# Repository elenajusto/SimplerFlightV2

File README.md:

# SimplerFlightV2

## Architecture

## Simulations
Simulations done using Falstad. Available at: https://www.falstad.com/circuit/

### Buzzer

hFE value of 250 

As per characteristics of FSB560A NPN BJT at https://www.digikey.com/en/products/detail/onsemi/FSB560A/1049460

### Camera Power

Beta value of 7.8

Assuming:
- RDS(on) (Ω) (use typical value): 0.16
- VGS where measured (V): 2.5
- Threshold (V) (use typical value): 3.3

As per characteristics of BSS816NWH6327XTSA1 N-MOSFET at https://www.digikey.com.au/en/products/detail/infineon-technologies/BSS816NWH6327XTSA1/5959970

## Microcontroller Pinout

## Schematic

### Root

### Microcontroller

### Power

### Sensors

### Storage

### Peripherals

### Headers

## Routing

## PCB

## Dimensions
94mm x 74mm

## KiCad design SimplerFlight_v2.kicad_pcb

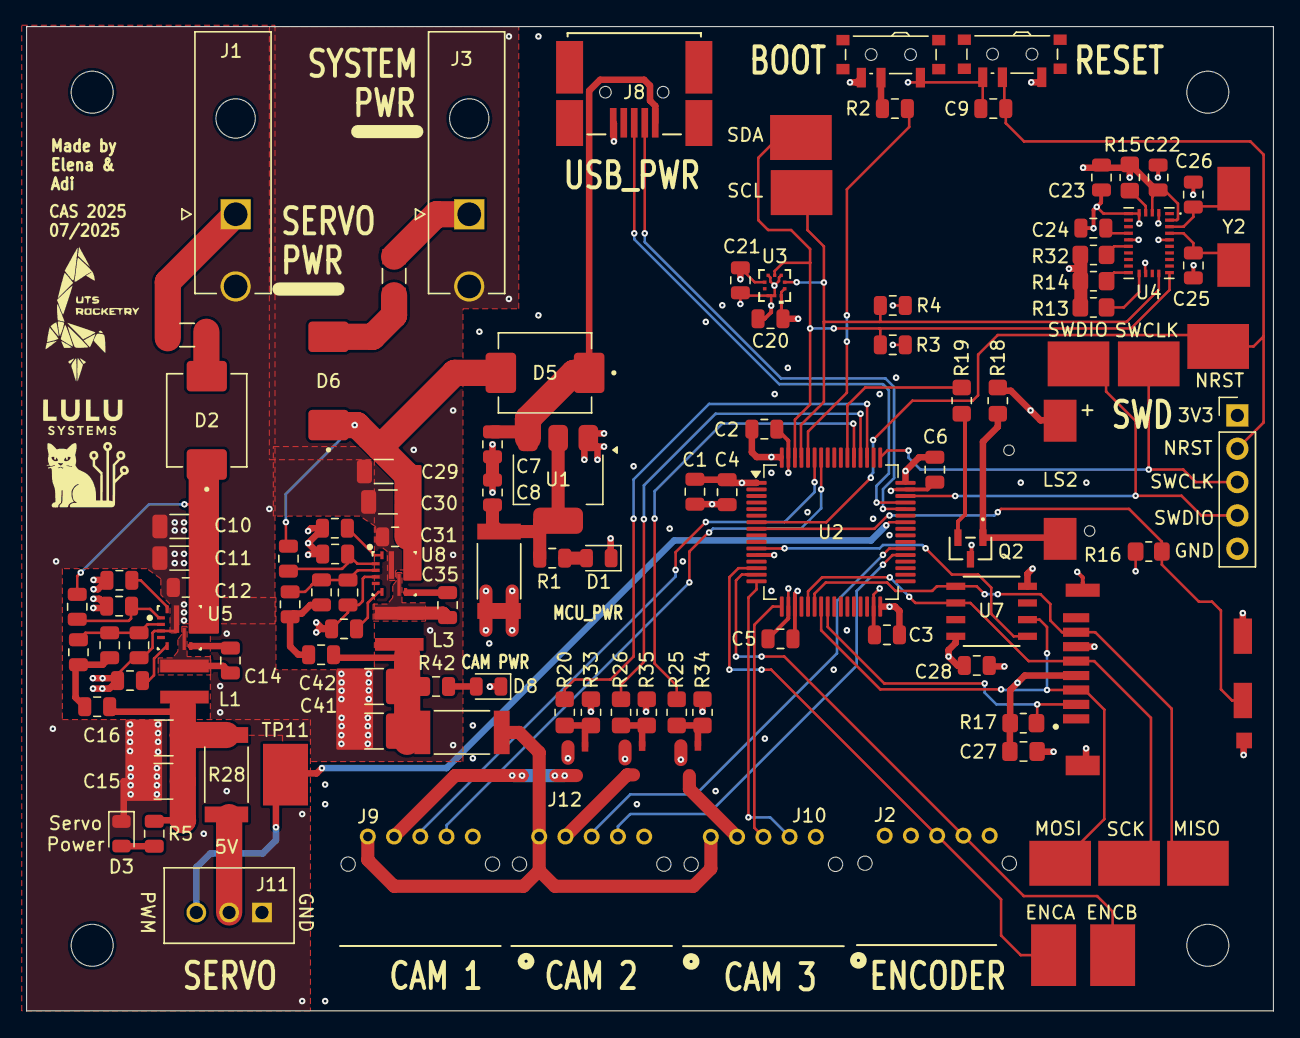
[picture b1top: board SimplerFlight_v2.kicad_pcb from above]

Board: 4 copper layers, 95.0 x 75.0 mm, 119 parts (0 on the bottom side), 74 nets.

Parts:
C1, C7: 10uF; C_0805_2012Metric
C2, C3, C4, C5, C6, C9, C20, C21, C22, C23, C24, C28: 100nF; C_0805_2012Metric
C8: 22uF; C_0805_2012Metric
C10, C11, C29, C30: 10uF; C_1206_3216Metric
C12, C14, C31, C35: 0.1uF; C_0805_2012Metric
C13, C34: 47nF; C_0805_2012Metric
C15, C16, C41, C42: 10uF; C_1210_3225Metric
C17, C40: 150pF; C_0805_2012Metric
C25, C26: 15pF; C_0805_2012Metric
C27: 100nF; C_0805_2012Metric_Pad1.18x1.45mm_HandSolder
D1: BLUE; LED_0805_2012Metric
D2, D5, D6: B540C-13-F; DIOM6959X245N
D3, D8: RED; LED_0805_2012Metric
ENCA: 5016; KEYSTONE_5016
ENCB: 5016; KEYSTONE_5016
F1, F3: C1F-5; FUSC3215X83N
H1, H2, H3, H4: MountingHole; MountingHole_3.2mm_M3
J1, J3: Battery 1; MOLEX_1724480002
J2: Encoder; CONN_S05B-PASK-2_JST
J8: USB; CON00317_5_MOL
J9, J10, J12: Cam 1; CONN_S05B-PASK-2_JST
J11: Servo; JST_B3B-XH-A
J13: SWD Header; PinHeader_1x05_P2.54mm_Vertical
J14: DM3CS-SF; HRS_DM3CS-SF
L1, L3: 3.3uH; WE-MAPI_4030
LS2: CBT-09427-SMT; CUI_CBT-09427-SMT
MISO: 5016; KEYSTONE_5016
MOSI: 5016; KEYSTONE_5016
NRST: 5016; KEYSTONE_5016
Q2: NPN; SSOT3_3X1P5_ONS
Q5, Q6, Q7: BSS816NWH6327XTSA1; SOT65P210X100-3N
R1, R3, R4, R5, R42: 1k5; C_0805_2012Metric
R2: 10k; C_0805_2012Metric
R6, R36: 169kR; C_0805_2012Metric
R7, R37: 36.1kR; C_0805_2012Metric
R8, R38: 52.3kR; C_0805_2012Metric
R9, R40: 49.9R; C_0805_2012Metric
R10, R41: 73.2kR; C_0805_2012Metric
R11, R39: 10kR; C_0805_2012Metric
R13, R14: 2.2kR; R_0805_2012Metric_Pad1.20x1.40mm_HandSolder
R15, R33, R34, R35: 10kR; R_0805_2012Metric_Pad1.20x1.40mm_HandSolder
R16, R17, R32: 10k; R_0805_2012Metric_Pad1.20x1.40mm_HandSolder
R18: 1kR; R_0805_2012Metric_Pad1.20x1.40mm_HandSolder
R19: 470; R_0805_2012Metric_Pad1.20x1.40mm_HandSolder
R20, R25, R26: 100R; R_0805_2012Metric_Pad1.20x1.40mm_HandSolder
R27, R28, R29: CSRN2512FKR500; RESC6331X70N
SCK: 5016; KEYSTONE_5016
SCL: 5016; KEYSTONE_5016
SDA: 5016; KEYSTONE_5016
SW1: Boot Switch; SW_SPDT_PCM12
SW2: System Reset; SW_SPDT_PCM12
SWCLK: 5016; KEYSTONE_5016
SWDIO: 5016; KEYSTONE_5016
TP11: 5016; KEYSTONE_5016
U1: AMS1117-3.3; SOT-223-3_TabPin2
U2: STM32F401RETx; LQFP-64_10x10mm_P0.5mm
U3: BMP581; QFN10_BMP581_BOS
U4: BNO085; IC_BNO085
U5, U8: TPS56A37RPAR; RPA0010A-MFG
U7: MX25V4006EM1I-13G; SOP8_150_MAC
Y2: Crystal; Crystal_SMD_0603-2Pin_6.0x3.5mm_HandSoldering

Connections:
/BOARD_3V3: C1.1, C2.1, C3.1, C4.1, C5.1, C6.1, C20.1, C21.1, C22.1, C23.1, C27.1, C28.1, J2.1, J13.1, J14.4 (VDD), LS2.P, R3.2, R4.2, R13.1, R14.1, R15.2, R16.1, R17.1, R18.2, R29.2, R32.1, R33.2, R34.2, R35.2, SW1.3 (C), SW2.1 (A), U2.1 (VBAT), U2.19 (VDD), U2.32 (VDD), U2.48 (VDD), U2.64 (VDD), U3.1 (VDDIO), U3.6 (CSB), U3.10 (VDD), U4.3 (VDD), U4.28 (VDDIO), U7.8 (VCC)
/Headers/SYS_JTCK-SWCLK: J13.3, SWCLK.TP, U2.49 (PA14)
/Headers/SYS_JTMS-SWDIO: J13.4, SWDIO.TP, U2.46 (PA13)
/Microcontroller/BOOT0: R2.2, U2.60 (BOOT0)
/Microcontroller/BUZZ: R19.1, U2.54 (PD2)
/Microcontroller/CAM_1_EN: R20.1, U2.51 (PC10)
/Microcontroller/CAM_2_EN: R25.1, U2.53 (PC12)
/Microcontroller/CAM_3_EN: R26.1, U2.52 (PC11)
/Microcontroller/ENC_A: ENCA.TP, J2.3, U2.14 (PA0)
/Microcontroller/ENC_B: ENCB.TP, J2.4, U2.15 (PA1)
/Microcontroller/FLASH_MEM_CS: U2.11 (PC3), U7.1 (CS#)
/Microcontroller/I2C1_SCL: R4.1, SCL.TP, U2.61 (PB8), U3.2 (SCK), U4.19 (H_SCL/SCK/RX)
/Microcontroller/I2C1_SDA: R3.1, SDA.TP, U2.62 (PB9), U3.4 (SDI), U4.20 (H_SDA/H_MISO/TX)
/Microcontroller/SD_DET: J14.9 (CD_SW), R16.2, U2.8 (PC0)
/Microcontroller/SD_MEM_CS: J14.2 (CD/DAT3), R17.2, U2.24 (PC4)
/Microcontroller/SERVO_PWM: J11.3, TP11.TP, U2.42 (PA9)
/Microcontroller/SP1_MISO: J14.7 (DAT0), MISO.TP, U2.22 (PA6), U7.5 (SI/SIO0)
/Microcontroller/SP1_MOSI: J14.3 (CMD), MOSI.TP, U2.23 (PA7), U7.2 (SO/SIO1)
/Microcontroller/SP1_SCK: J14.5 (CLK), SCK.TP, U2.21 (PA5), U7.6 (SCLK)
/Microcontroller/SW_BOOT0: R2.1, SW1.2 (B)
/Microcontroller/USART1_RX: J9.3, U2.59 (PB7)
/Microcontroller/USART1_TX: J9.4, U2.58 (PB6)
/Microcontroller/USART2_RX: J10.3, U2.17 (PA3)
/Microcontroller/USART2_TX: J10.4, U2.16 (PA2)
/Microcontroller/USART6_RX: J12.3, U2.38 (PC7)
/Microcontroller/USART6_TX: J12.4, U2.37 (PC6)
/Microcontroller/USB_DN: J8.2, U2.44 (PA11)
/Microcontroller/USB_DP: J8.3, U2.45 (PA12)
/Peripherals/5V_CAM: J9.1, J10.1, J12.1, R27.2
/Peripherals/5V_SERVO: J11.2, R28.2
/Power/5V_CAM: C41.1, C42.1, L3.2, R27.1, R40.1, R42.1
/Power/5V_SERVO: C15.1, C16.1, L1.2, R5.1, R9.1, R28.1
/Power/+3V3: C8.1, R1.1, R29.1, U1.2 (VO)
/Power/BAT_1: D2.A, F1.2
/Power/BAT_2: D6.A, F3.2
/Power/BT_CAM: C35.1, U8.7 (BOOT)
/Power/BT_SERVO: C14.1, U5.7 (BOOT)
/Power/EN_CAM_PWR: R36.2, R37.1, U8.1 (EN)
/Power/EN_SERVO_PWR: R6.2, R7.1, U5.1 (EN)
/Power/FB_CAM_PWR: C40.2, R39.1, R41.2, U8.2 (FB)
/Power/FB_SERVO: C17.2, R10.2, R11.1, U5.2 (FB)
/Power/MODE_CAM: R38.2, U8.10 (MODE)
/Power/MODE_SRVO: R8.2, U5.10 (MODE)
/Power/SS_CAM: C34.1, U8.5 (SS)
/Power/SS_SERVO: C13.1, U5.5 (SS)
/Power/SW_CAM_PWR: C35.2, L3.1, U8.6 (SW)
/Power/SW_SERVO: C14.2, L1.1, U5.6 (SW)
/Power/VBUS_MCU: C7.1, D5.C, J8.1, U1.3 (VI)
/Power/VIN_CAM: C29.1, C30.1, C31.1, D5.A, D6.C, R36.1, U8.8 (VIN)
/Power/VIN_SERVO: C10.1, C11.1, C12.1, D2.C, R6.1, U5.8 (VIN)
GND: C1.2, C2.2, C3.2, C4.2, C5.2, C6.2, C7.2, C8.2, C9.2, C10.2, C11.2, C12.2, C13.2, C15.2, C16.2, C20.2, C21.2, C22.2, C23.2, C24.1, C25.2, C26.2, C27.2, C28.2, C29.2, C30.2, C31.2, C34.2, C41.2, C42.2, D1.1 (K), D3.1 (K), D8.1 (K), J1.2, J2.2, J3.2, J8.5, J11.1, J13.5, J14.6 (VSS), J14.S1 (GND), J14.S2 (GND__1), J14.S3 (GND__2), J14.S5 (GND__3), Q2.3 (E), Q5.2 (S), Q6.2 (S), Q7.2 (S), R7.2, R8.1, R11.2, R37.2, R38.1, R39.2, SW1.1 (A), SW2.3 (C), U1.1 (GND), U2.12 (VSSA), U2.18 (VSS), U2.31 (VSS), U2.47 (VSS), U2.63 (VSS), U3.3 (VSS), U3.5 (SDO), U3.8 (VSS), U3.9 (VSS), U4.2 (GND), U4.5 (PS1), U4.6 (PS0/WAKE), U4.10 (CLKSEL0), U4.17 (SA0/H_MOSI), U4.25 (GNDIO), U5.3 (AGND), U5.9 (PGND), U7.4 (GND), U8.3 (AGND), U8.9 (PGND)
NRST: C9.1, J13.2, NRST.TP, SW2.2 (B), U2.7 (NRST)
unnamed: C17.1, R9.2, R10.1
unnamed: C40.1, R40.2, R41.1
unnamed: D1.2 (A), R1.2
unnamed: D3.2 (A), R5.2
unnamed: D8.2 (A), R42.2
unnamed: F1.1, J1.1
unnamed: F3.1, J3.1
unnamed: Q2.2 (B), R19.2
unnamed: LS2.M, Q2.1 (C), R18.1
unnamed: J9.2, Q5.3 (D)
unnamed: Q5.1 (G), R20.2, R33.1
unnamed: J10.2, Q6.3 (D)
unnamed: Q6.1 (G), R25.2, R34.1
unnamed: J12.2, Q7.3 (D)
unnamed: Q7.1 (G), R26.2, R35.1
unnamed: C24.2, U4.9 (CAP)
unnamed: R14.2, U4.15 (ENV_SCL)
unnamed: R13.2, U4.16 (ENV_SDA)
unnamed: C26.1, U4.27 (XIN32), Y2.2
unnamed: C25.1, U4.26 (XOUT32/CLKSEL1), Y2.1
unnamed: R15.1, U4.4 (~BOOT)
unnamed: R32.2, U4.11 (~RST)

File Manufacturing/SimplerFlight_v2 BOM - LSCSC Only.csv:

JLCPCB Part #,Comment,Footprint,Designator
C28233,100nF,Capacitor_SMD:C_0805_2012Metric,"C2,C3,C4,C5,C6,C9,C20,C21,C18,C19,C27,C28"
C45783,22uF,Capacitor_SMD:C_0805_2012Metric," ""C1"
C13585,10uF,Capacitor_SMD:C_1206_3216Metric,"C10,C11,C29,C30"
C28378,0.1uF,Capacitor_SMD:C_0805_2012Metric,"C12,C14,C31,C35"
C53134,47nF,Capacitor_SMD:C_0805_2012Metric,"C13,C34"
C138687,10uF,Capacitor_SMD:C_1210_3225Metric,"C15,C16,C41,C42"
C1716,150pF,Capacitor_SMD:C_0805_2012Metric,"C17,C40"
C107110,15pF,Capacitor_SMD:C_0805_2012Metric,"C25,C26"
C2297,BLUE,LED_SMD:LED_0805_2012Metric,D1
C72264,B540C-13-F,B540C_13_F:DIOM6959X245N,"D2,D5,D6"
C2286,RED,LED_SMD:LED_0805_2012Metric,"D3,D8"
" 	C57525",C1F-5,C1F_5:FUSC3215X83N,"F1,F3"
C5188718,Battery 1,1724480002:MOLEX_1724480002,"J1,J3"
C598519,USB,custom,J4
C2845127,Cam 1,S05B_PASK_2_LF__SN_:CONN_S05B-PASK-2_JST,"J2, J9,J10,J12"
C144394,Servo,B3B_XH_A:JST_B3B-XH-A,J11
C202111,DM3CS-SF,DM3CS_SF:HRS_DM3CS-SF,J14
C39676082,3.3uH,74438357033:WE-MAPI_4030,"L1,L3"
C95299,Huaneng MLT-7525,LS2,LS2
C236952,NPN,FSB560A:SSOT3_3X1P5_ONS,Q2
C22366684,BSS816NWH6327XTSA1,SOT65P210X100-3N,"Q5,Q6,Q7"
C4310,1k5,Capacitor_SMD:C_0805_2012Metric,"R1,R3,R4,R5,R42"
C2933337,169kR,Capacitor_SMD:C_0805_2012Metric,"R6,R36"
C2758300,52.3kR,Capacitor_SMD:C_0805_2012Metric,"R8,R38"
C269747,49.9R,Capacitor_SMD:C_0805_2012Metric,"R9,R40"
C865640,73.2kR,Capacitor_SMD:C_0805_2012Metric,"R10,R41"
C17414,10kR,Capacitor_SMD:C_0805_2012Metric,"R2, R11,R39, R15,R33,R34,R35, R16,R17,R32"
C17513,1kR,Resistor_SMD:R_0805_2012Metric_Pad1.20x1.40mm_HandSolder,R18
C17710,470,Resistor_SMD:R_0805_2012Metric_Pad1.20x1.40mm_HandSolder,R19
C17408,100R,Resistor_SMD:R_0805_2012Metric_Pad1.20x1.40mm_HandSolder,"R20,R25,R26"
C346810,CSRN2512FKR500,CSRN2512FKR500:RESC6331X70N,"R27,R28,R29"
 C221841,Boot Switch,Button_Switch_SMD:SW_SPDT_PCM12,"SW1, SW2"
C238129,5016,5016:KEYSTONE_5016,"TP1,TP2,TP3,TP4,TP5,TP6,TP7,TP8,TP11,TP12,TP13"
C6186,AMS1117-3.3,Package_TO_SOT_SMD:SOT-223-3_TabPin2,U1
C116978,STM32F401RETx,Package_QFP:LQFP-64_10x10mm_P0.5mm,U2
C5362283,BMP581,BMP581:QFN10_BMP581_BOS,U3
C2836813,BMI270," 	LGA-14(2.5x3)",U4
 C22392669,TPS56A37RPAR,RPA0010A-MFG,"U5,U8"
C152601,MX25V4006EM1I-13G,SOP8_150_MAC,U7
C130253,32 kHz,ABS07_32_768KHZ_T:XTAL_ABS07-32.768KHZ-T,Y2

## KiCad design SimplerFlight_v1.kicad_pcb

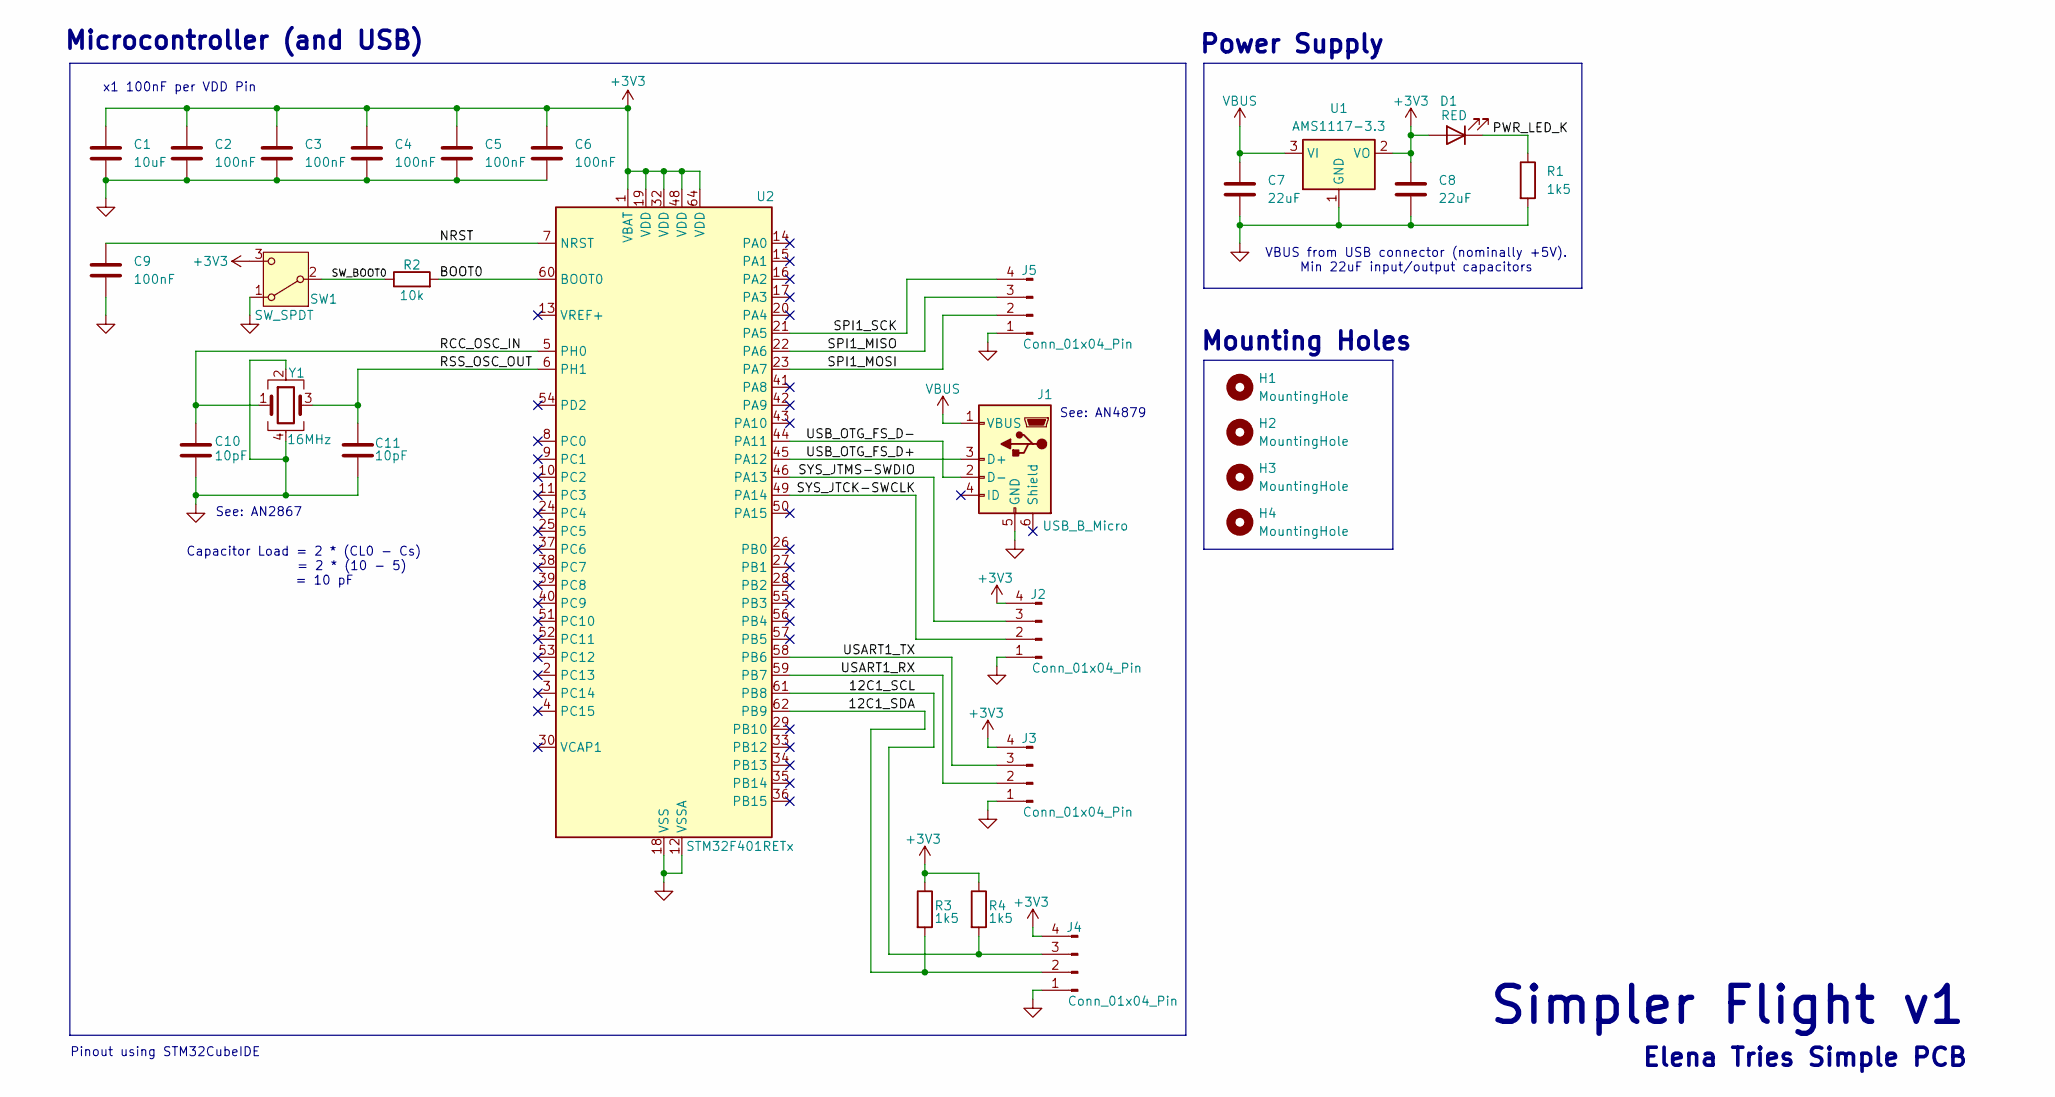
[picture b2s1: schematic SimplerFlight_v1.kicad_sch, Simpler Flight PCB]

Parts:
C1: 10uF; C_0805_2012Metric
C2, C3, C4, C5, C6, C9: 100nF; C_0805_2012Metric
C7, C8: 22uF; C_0805_2012Metric
C10, C11: 10pF; C_0805_2012Metric
D1: RED; LED_0805_2012Metric
H1, H2, H3, H4: MountingHole; MountingHole_2.2mm_M2
J1: USB_B_Micro; USB_Micro-B_Wuerth_629105150521
J2, J3, J4, J5: Conn_01x04_Pin; PinHeader_1x04_P2.54mm_Vertical
R1, R3, R4: 1k5; C_0805_2012Metric
R2: 10k; C_0805_2012Metric
SW1: SW_SPDT; SW_SPDT_PCM12
U1: AMS1117-3.3; SOT-223-3_TabPin2
U2: STM32F401RETx; LQFP-64_10x10mm_P0.5mm
Y1: 16MHz; Crystal_SMD_3225-4Pin_3.2x2.5mm

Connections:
+3V3: C1.1, C2.1, C3.1, C4.1, C5.1, C6.1, C8.1, D1.2 (A), J2.4, J3.4, J4.4, R3.1, R4.1, SW1.3 (C), U1.2 (VO), U2.1 (VBAT), U2.19 (VDD), U2.32 (VDD), U2.48 (VDD), U2.64 (VDD)
/12C1_SCL: J4.3, R4.2, U2.61 (PB8)
/12C1_SDA: J4.2, R3.2, U2.62 (PB9)
/BOOT0: R2.2, U2.60 (BOOT0)
/NRST: C9.1, U2.7 (NRST)
/PWR_LED_K: D1.1 (K), R1.1
/RCC_OSC_IN: C10.1, U2.5 (PH0), Y1.1
/RSS_OSC_OUT: C11.1, U2.6 (PH1), Y1.3
/SPI1_MISO: J5.3, U2.22 (PA6)
/SPI1_MOSI: J5.2, U2.23 (PA7)
/SPI1_SCK: J5.4, U2.21 (PA5)
/SW_BOOT0: R2.1, SW1.2 (B)
/SYS_JTCK-SWCLK: J2.2, U2.49 (PA14)
/SYS_JTMS-SWDIO: J2.3, U2.46 (PA13)
/USART1_RX: J3.2, U2.59 (PB7)
/USART1_TX: J3.3, U2.58 (PB6)
/USB_OTG_FS_D+: J1.3 (D+), U2.45 (PA12)
/USB_OTG_FS_D-: J1.2 (D-), U2.44 (PA11)
GND: C1.2, C2.2, C3.2, C4.2, C5.2, C6.2, C7.2, C8.2, C9.2, C10.2, C11.2, J1.5 (GND), J2.1, J3.1, J4.1, J5.1, R1.2, SW1.1 (A), U1.1 (GND), U2.12 (VSSA), U2.18 (VSS), U2.31 (VSS), U2.47 (VSS), U2.63 (VSS), Y1.2, Y1.4
VBUS: C7.1, J1.1 (VBUS), U1.3 (VI)

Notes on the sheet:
x1 100nF per VDD Pin
Pinout using STM32CubeIDE
VBUS from USB connector (nominally +5V). Min 22uF input/output capacitors
Capacitor Load = 2 * (CL0 - Cs) = 2 * (10 - 5) = 10 pF
Mounting Holes
See: AN4879
Elena Tries Simple PCB
See: AN2867
Power Supply
Simpler Flight v1
Microcontroller (and USB)

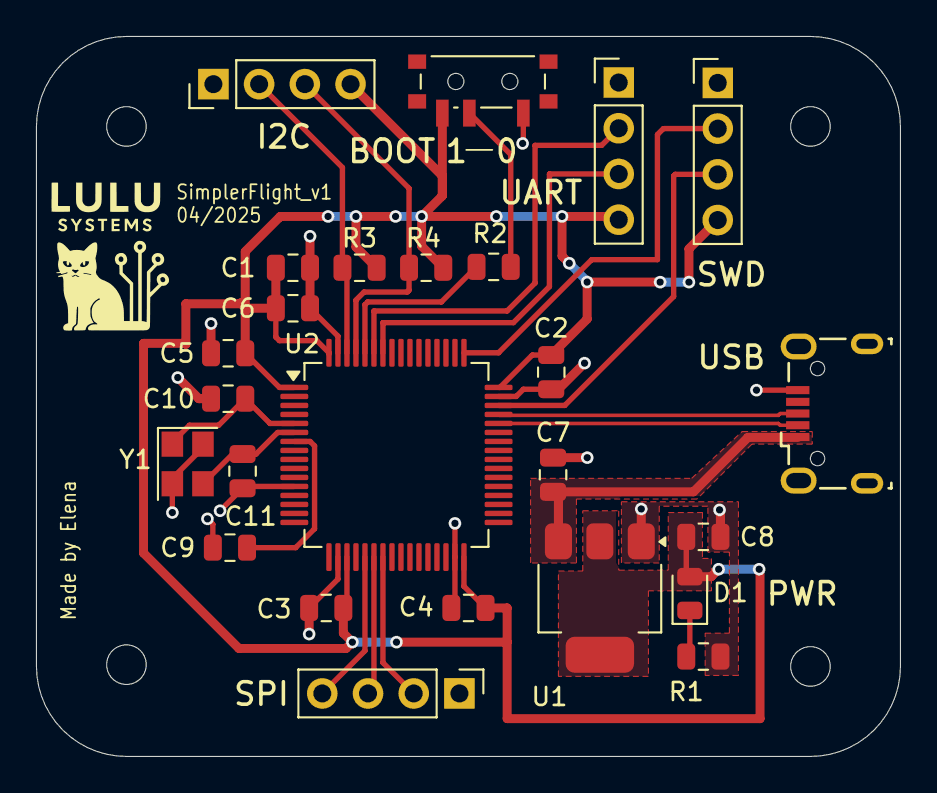
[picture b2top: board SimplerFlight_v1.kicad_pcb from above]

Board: 2 copper layers, 48.0 x 40.0 mm, 29 parts (0 on the bottom side), 20 nets.

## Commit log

2025-06-14 Init files
2025-06-16 Clean and rename to V2
2025-06-16 Add USB Mini B to replace USB Micro
2025-06-16 Image folder and edit readme
2025-06-16 Edit README
2025-06-16 Update readme and some silskreen labeles
2025-06-16 readme
2025-06-16 Fix name
2025-06-23 Reorganisation and draft of power supply
2025-06-24 Remove redundant diode for camera supply
2025-06-25 Upload architecture diagram, start sensor schematic, add simulation files
2025-07-02 addecd stuff
2025-07-04 Initiliase main components
2025-07-05 Update schematic, pending power sims, updated README
2025-07-07 Remove transistor enable for servo power. Added falstad sim files
2025-07-07 Updated schematics
2025-07-07 added schotkey diode for encoder power
2025-07-07 Update buzzer circuit and add simulation
2025-07-07 remove schotkey diodes from servo and encoder interfaces
2025-07-07 Add camera power sim and made gitignore file
2025-07-07 Stop tracking temp files and backup file
2025-07-07 Modify README to point to correct transistor used for camera
2025-07-07 Add link to falstad
2025-07-07 Redo footprints and add mosfet for camera power control
2025-07-07 Remove more junk files from git tracking
2025-07-07 Refactor buzzer sim to use single terminal sources
2025-07-07 Update simulation for buzzer NPN transistor to use correct hFE value
2025-07-07 use another shotkey diode for battery to usb intersection for mcu power
2025-07-07 Use different flash chip with nicer documentation
2025-07-07 labels for storage schematic
2025-07-07 Add net names to power
2025-07-07 Use heirarchical labels
2025-07-08 Broke headers into own heiarchicial sheet
2025-07-08 add mcu pinout diagram
2025-07-08 Added voltage/signal test points
2025-07-08 Removed external highspeed clock
2025-07-08 Initial layout for PCB components, updated README with images. Removed some test points and headers from final layout. Pending addition of buzzer. Pending additional power testing and pending routing.
2025-07-08 Update images to show updated schematics using hierarchical pins for power lines
2025-07-13 Redo layout and redoing buck converters
2025-07-13 Udpate power schematic
2025-07-14 Layout
2025-07-14 Update screenshots and addeed 3D files
2025-07-14 Removed uncvessary test points and headerrs. Added missing values. Update images of schematics
2025-07-14 Add dimensions
2025-07-15 Sync
2025-07-16 Routing for cam buck converter
2025-07-16 Routes for power
2025-07-16 More routing - sync
2025-07-16 Re-arranged sensor, storage and peripheral component layout
2025-07-16 more routing
2025-07-21 symc
2025-07-21 Finish all essential routing
2025-07-23 Adi made some fixes to schematic
2025-07-23 Update cam 2 and cam 3 schematic
2025-07-23 CLEAN ROUTES
2025-07-23 Update capacitor model for Cin for servo motor power supply
2025-07-23 Update Cinx for servo motor power supply
2025-07-23 Update Cout models for servo motor power and extended pground
2025-07-23 update inductor
2025-07-23 Redo layout for servo buck converter
2025-07-23 Sync layout
2025-07-24 Sync more routing
2025-07-25 Revised to improve buck converters and free up space on board
    Fixed overvoltage error on encoder (5v -> 3v)
2025-07-26 jsut need to wire test points
2025-07-26 Update cad model and readme images
2025-08-02 Fix foot print for IMU clock
2025-08-02 Revised routing
    Minor changes to signal routing. Cleared out drc errors
2025-08-05 Use LCSC parts only
2025-08-05 Add finalised LSCSC BOM
2025-08-05 Update csv files to match LSCSC format
2025-10-01 Fixed trace spacing DFM issue with bottom copper traces for USB differentials as per JLCDFM
2025-10-05 Fixing DFM issues as per JLC tool
2025-10-06 Fix most of DANGER status for solder mask layer JLC DFM
2025-10-06 All solder mask layer analyisis moved away from DANGER
2025-10-06 Move silksreen to hole DFM issues OUT OF DANGER
2025-10-06 Move silksreen line width DFM issues OUT OF DANGER
2025-10-06 Update PCB images
2025-10-06 include BOM
